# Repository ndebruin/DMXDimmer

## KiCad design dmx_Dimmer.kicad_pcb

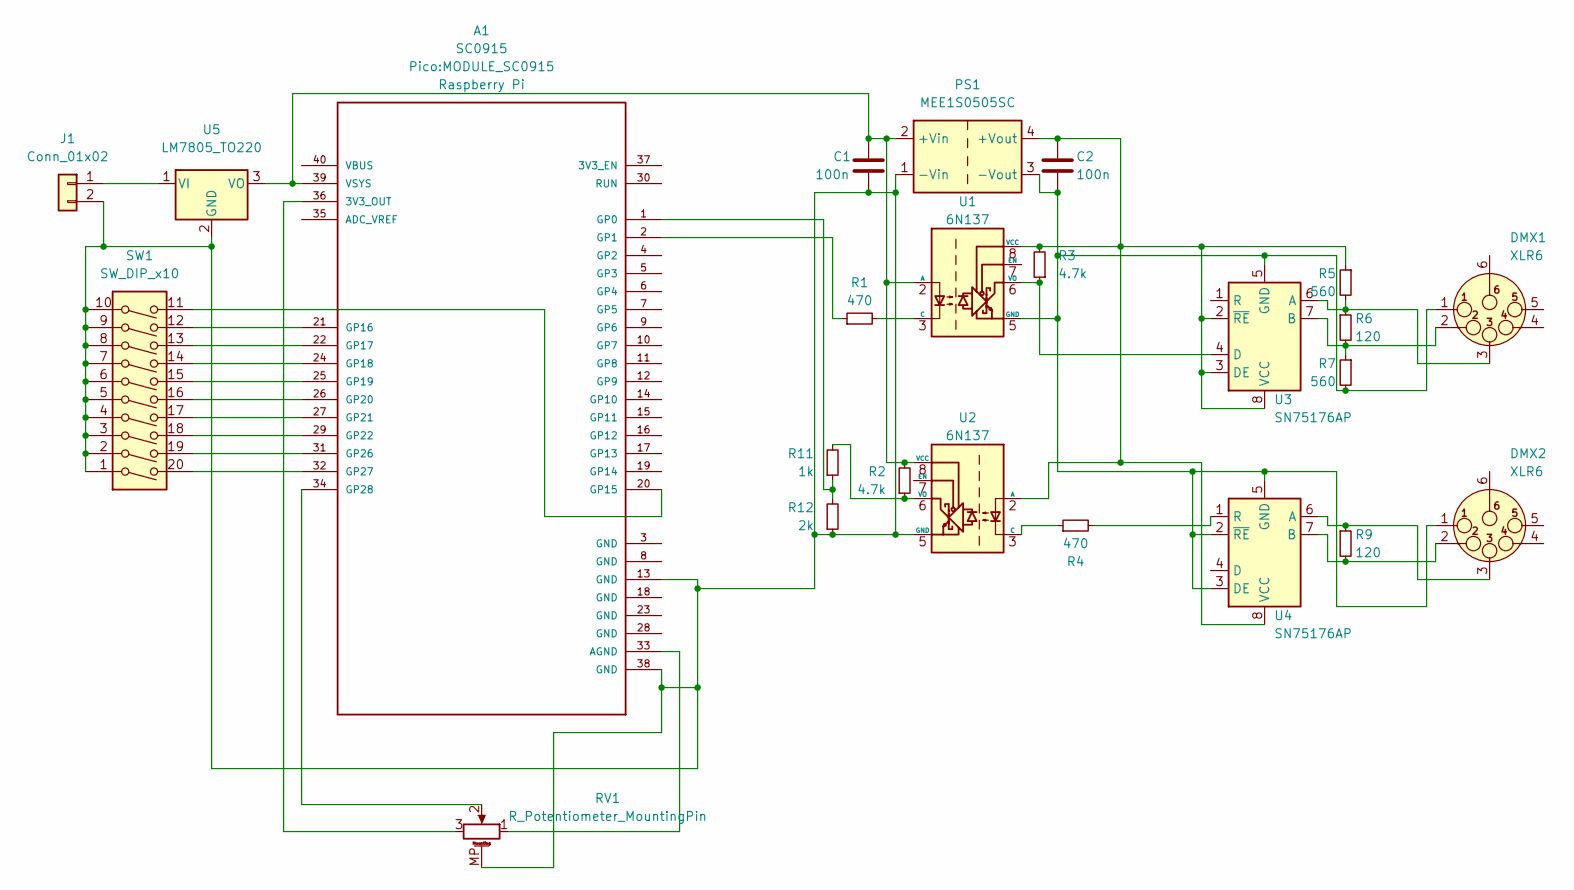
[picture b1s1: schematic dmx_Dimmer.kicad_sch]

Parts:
A1: SC0915; MODULE_SC0915; PARTREV 1.6
C1, C2: 100n; C_Disc_D3.8mm_W2.6mm_P2.50mm
DMX1, DMX2: XLR6; Jack_XLR_Neutrik_NC5FAH_Horizontal
J1: Conn_01x02
PS1: MEE1S0505SC; Converter_DCDC_Murata_MEE1SxxxxSC_THT
R1, R4: 470; R_0805_2012Metric_Pad1.20x1.40mm_HandSolder
R2, R3: 4.7k; R_0805_2012Metric_Pad1.20x1.40mm_HandSolder
R5, R7: 560; R_0805_2012Metric_Pad1.20x1.40mm_HandSolder
R6, R9: 120; R_0805_2012Metric_Pad1.20x1.40mm_HandSolder
R11: 1k; R_0805_2012Metric_Pad1.20x1.40mm_HandSolder
R12: 2k; R_0805_2012Metric_Pad1.20x1.40mm_HandSolder
RV1: R_Potentiometer_MountingPin
SW1: SW_DIP_x10; SW_DIP_SPSTx10_Slide_9.78x27.58mm_W7.62mm_P2.54mm
U1, U2: 6N137; DIP-8_W7.62mm
U3, U4: SN75176AP; SOIC-8_3.9x4.9mm_P1.27mm
U5: LM7805_TO220; TO-220-3_Vertical

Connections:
unnamed: A1.20 (GP15), SW1.11
unnamed: A1.21 (GP16), SW1.12
unnamed: A1.22 (GP17), SW1.13
unnamed: A1.24 (GP18), SW1.14
unnamed: A1.25 (GP19), SW1.15
unnamed: A1.26 (GP20), SW1.16
unnamed: A1.27 (GP21), SW1.17
unnamed: A1.29 (GP22), SW1.18
unnamed: A1.31 (GP26), SW1.19
unnamed: A1.32 (GP27), SW1.20
unnamed: A1.39 (VSYS), C1.1, PS1.2 (+Vin), R2.2, U1.2 (A), U2.8 (VCC), U5.3 (VO)
unnamed: A1.13 (GND), A1.38 (GND), C1.2, J1.2, PS1.1 (-Vin), R12.1, RV1.MP (MountPin), SW1.1, SW1.2, SW1.3, SW1.4, SW1.5, SW1.6, SW1.7, SW1.8, SW1.9, SW1.10, U2.5 (GND), U5.2 (GND)
unnamed: C2.1, PS1.4 (+Vout), R3.2, R5.1, U1.8 (VCC), U2.2 (A), U3.2 (~RE), U3.3 (DE), U3.8 (VCC), U4.8 (VCC)
unnamed: C2.2, DMX1.1, DMX2.1, PS1.3 (-Vout), R7.2, U1.5 (GND), U3.5 (GND), U4.2 (~RE), U4.3 (DE), U4.5 (GND)
unnamed: DMX1.2, R6.2, R7.1, U3.7 (B)
unnamed: DMX1.3, R5.2, R6.1, U3.6 (A)
unnamed: DMX2.2, R9.2, U4.7 (B)
unnamed: DMX2.3, R9.1, U4.6 (A)
unnamed: J1.1, U5.1 (VI)
unnamed: A1.2 (GP1), R1.1
unnamed: R1.2, U1.3 (C)
unnamed: R2.1, R11.2, U2.6 (VO)
unnamed: R3.1, U1.6 (VO), U3.4 (D)
unnamed: R4.1, U2.3 (C)
unnamed: R4.2, U4.1 (R)
unnamed: A1.1 (GP0), R11.1, R12.2
unnamed: A1.33 (AGND), RV1.1
unnamed: A1.34 (GP28), RV1.2
unnamed: A1.36 (3V3_OUT), RV1.3

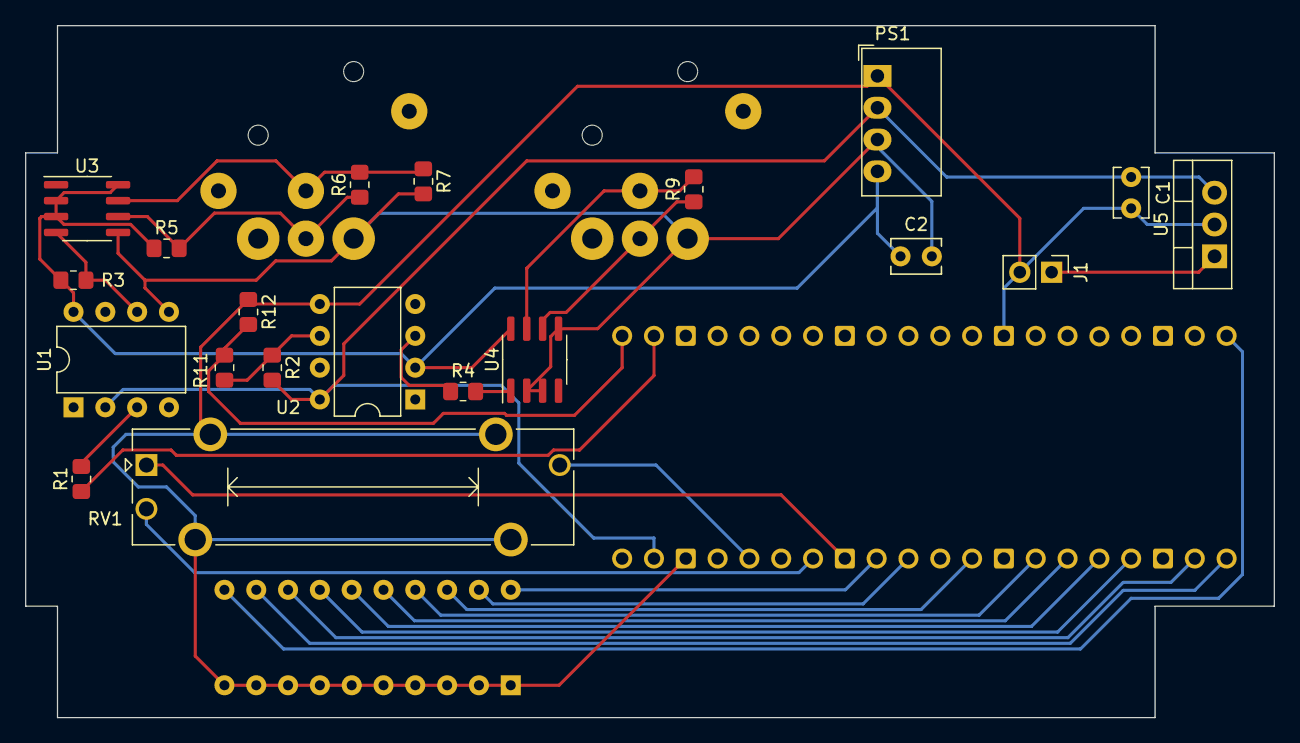
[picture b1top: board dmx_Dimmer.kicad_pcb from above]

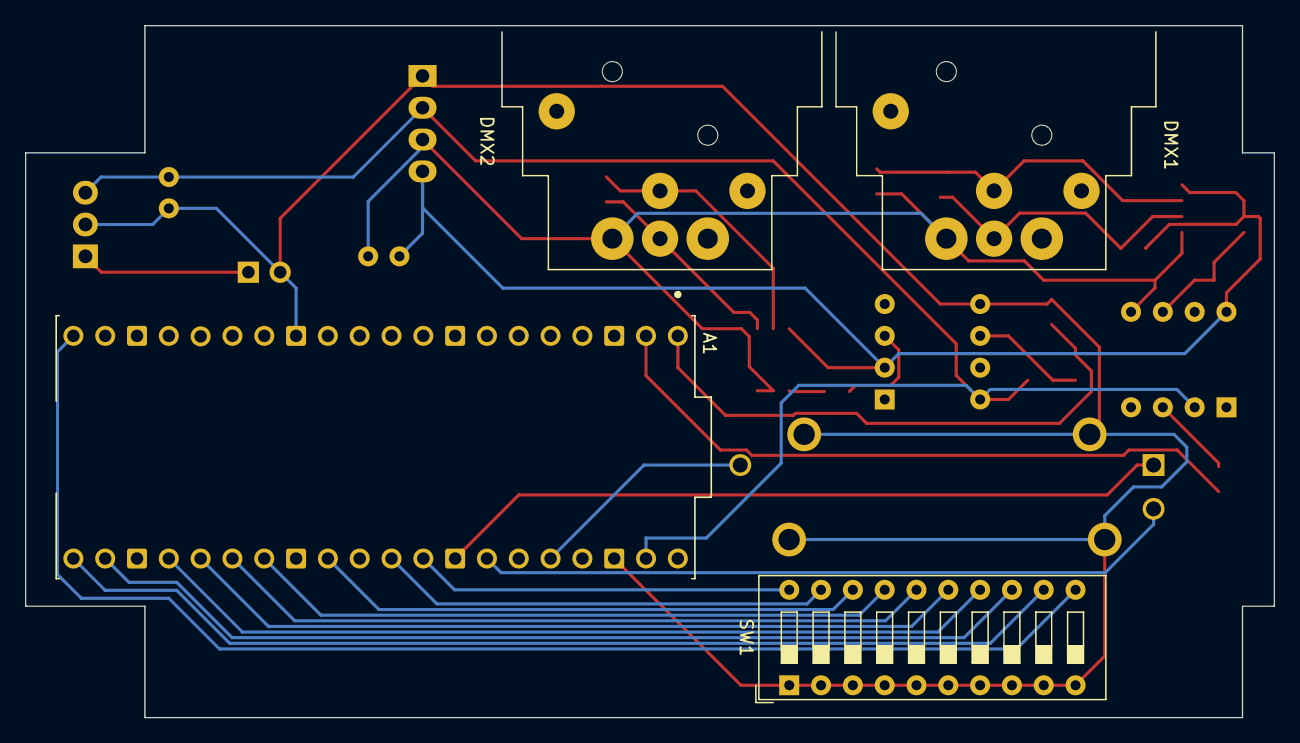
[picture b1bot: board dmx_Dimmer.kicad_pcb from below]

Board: 2 copper layers, 99.7 x 55.2 mm, 24 parts (4 on the bottom side), 29 nets.

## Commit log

2024-03-18 Add KiCad Files
2024-03-18 Add firmware
